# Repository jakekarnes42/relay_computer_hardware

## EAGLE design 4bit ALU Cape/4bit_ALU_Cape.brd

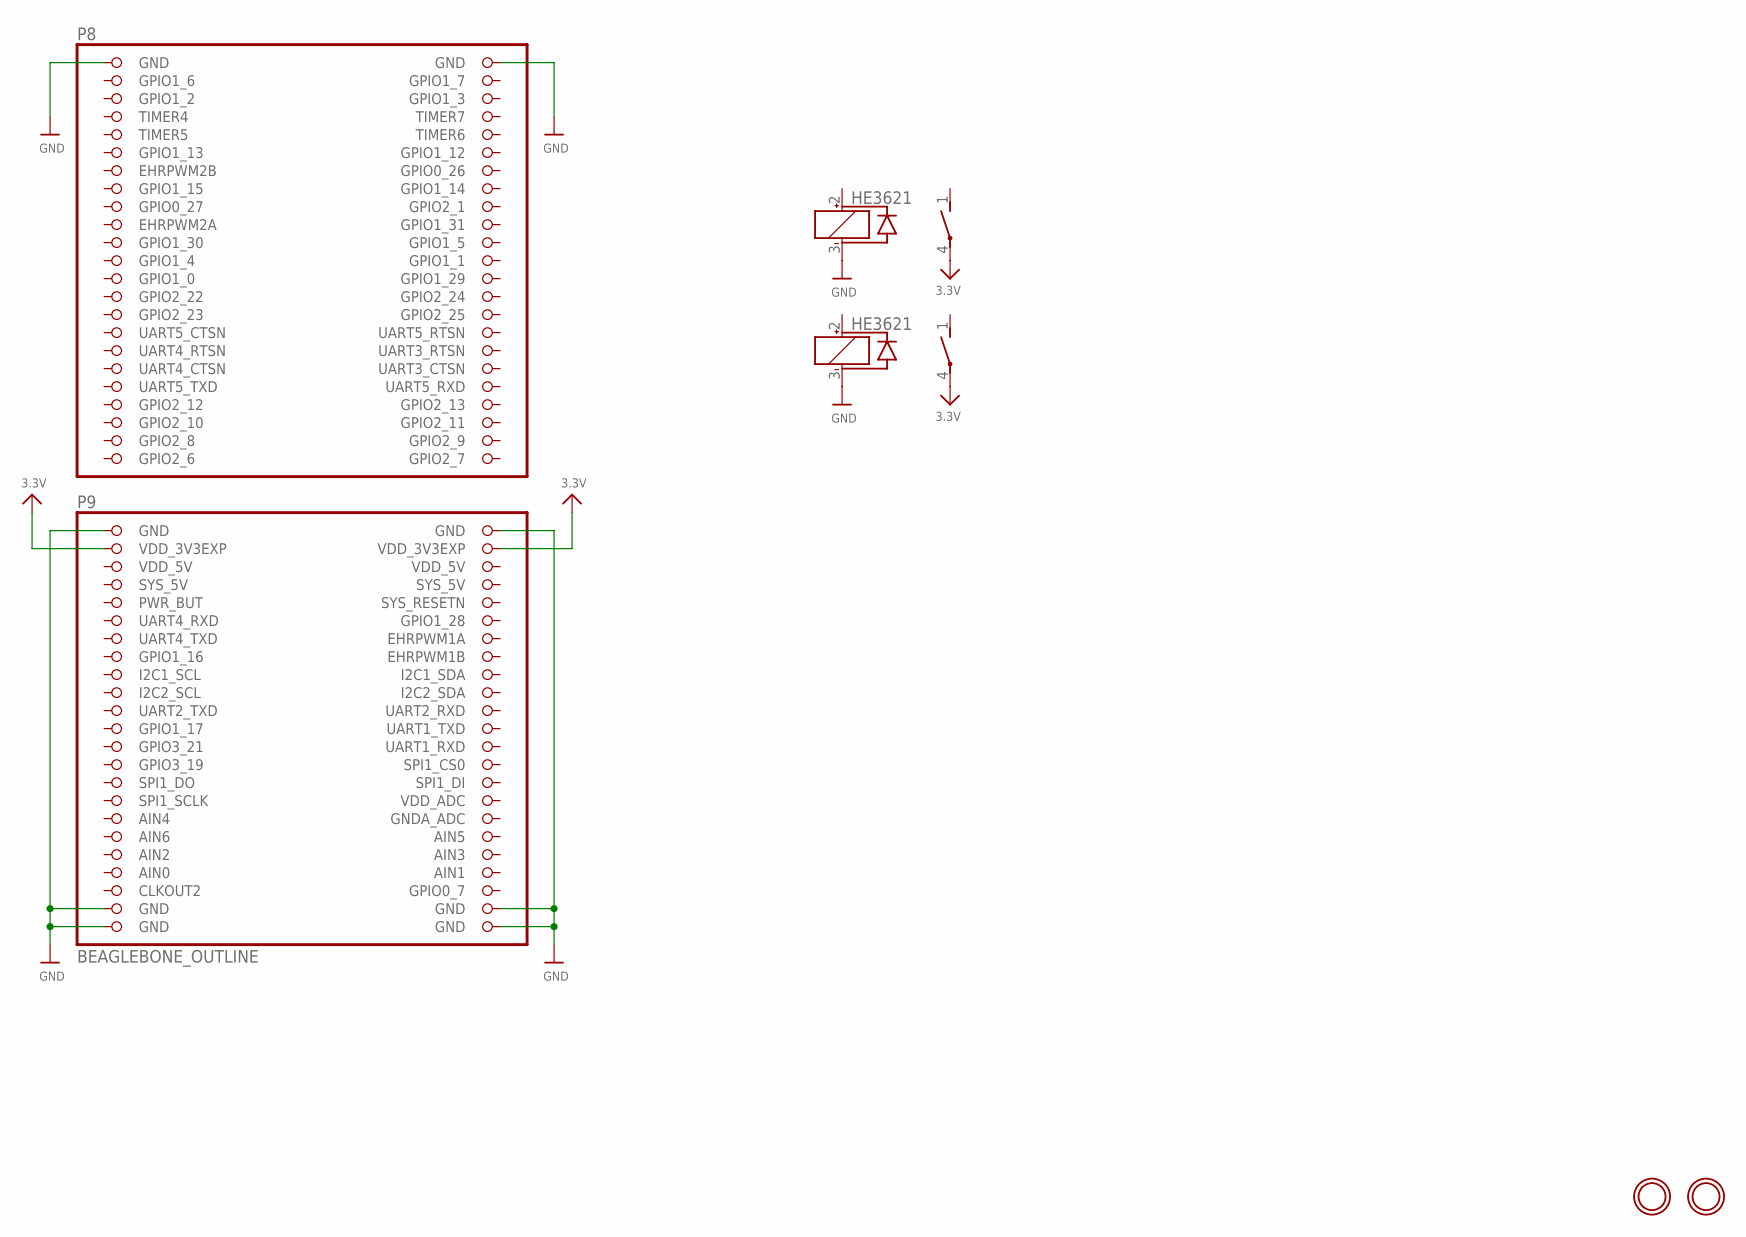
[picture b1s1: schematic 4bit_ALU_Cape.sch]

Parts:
K1, K2: HE3621
U: BEAGLEBONE_OUTLINE; BEAGLEBONE_SHIELD
U$22, U$23: MOUNTINGHOLE3.0THIN; MOUNTINGHOLE_3.0_PLATEDTHIN

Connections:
3.3V: K1.4, K2.4, U.49 (VDD_3V3EXP), U.50 (VDD_3V3EXP)
AIN0: U.85 (AIN0)
AIN3: U.84 (AIN3)
GND: K1.3 (-), K2.3 (-), U.1 (GND), U.2 (GND), U.47 (GND), U.48 (GND), U.89 (GND), U.90 (GND), U.91 (GND), U.92 (GND)
GPIO1_6: U.3 (GPIO1_6)
GPIO1_7: U.4 (GPIO1_7)
GPIO2_6: U.45 (GPIO2_6)
GPIO2_7: U.46 (GPIO2_7)
GPIO2_8: U.43 (GPIO2_8)
GPIO2_9: U.44 (GPIO2_9)
GPIO2_11: U.42 (GPIO2_11)
VDD_5V: U.51 (VDD_5V), U.52 (VDD_5V)

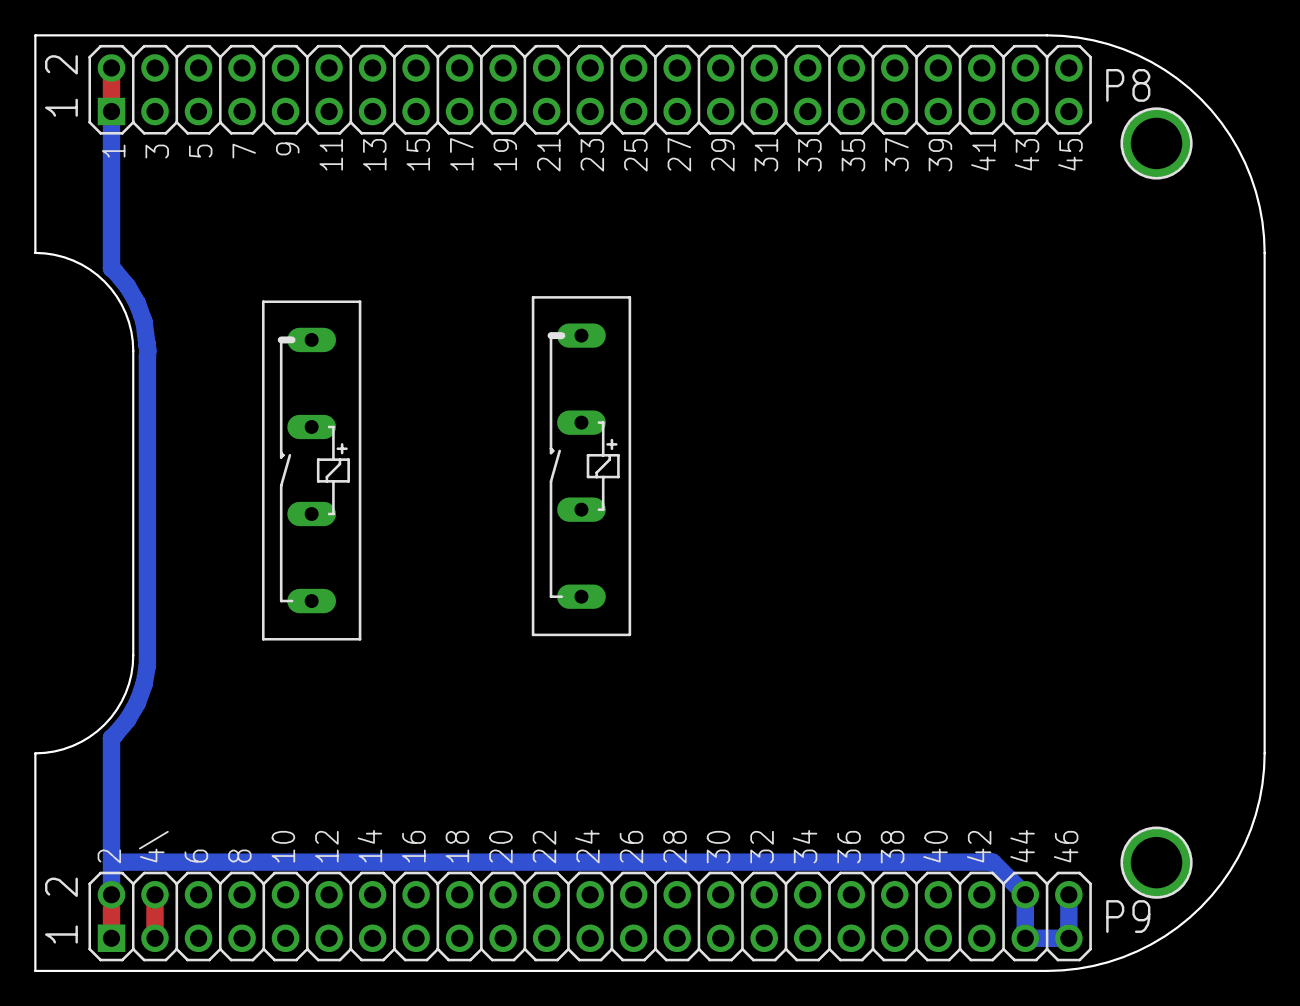
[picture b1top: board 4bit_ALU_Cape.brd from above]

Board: 2 copper layers, 71.8 x 54.6 mm, 5 parts (0 on the bottom side), 3 nets.

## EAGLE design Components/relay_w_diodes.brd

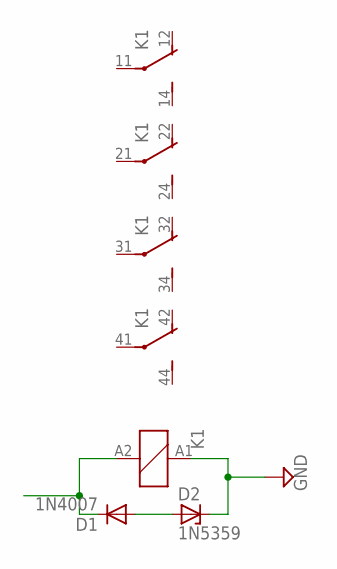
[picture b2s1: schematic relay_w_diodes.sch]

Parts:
D1: 1N4007; DO41-10
D2: 1N5359; C1702-15
K1: PY14-02

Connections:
D$1: D1.A, D2.A
GND: D2.C, K1.A1 (1)
IN: D1.C, K1.A2 (2)

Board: 2 copper layers, 3 parts (0 on the bottom side), 3 nets, no tracks yet.

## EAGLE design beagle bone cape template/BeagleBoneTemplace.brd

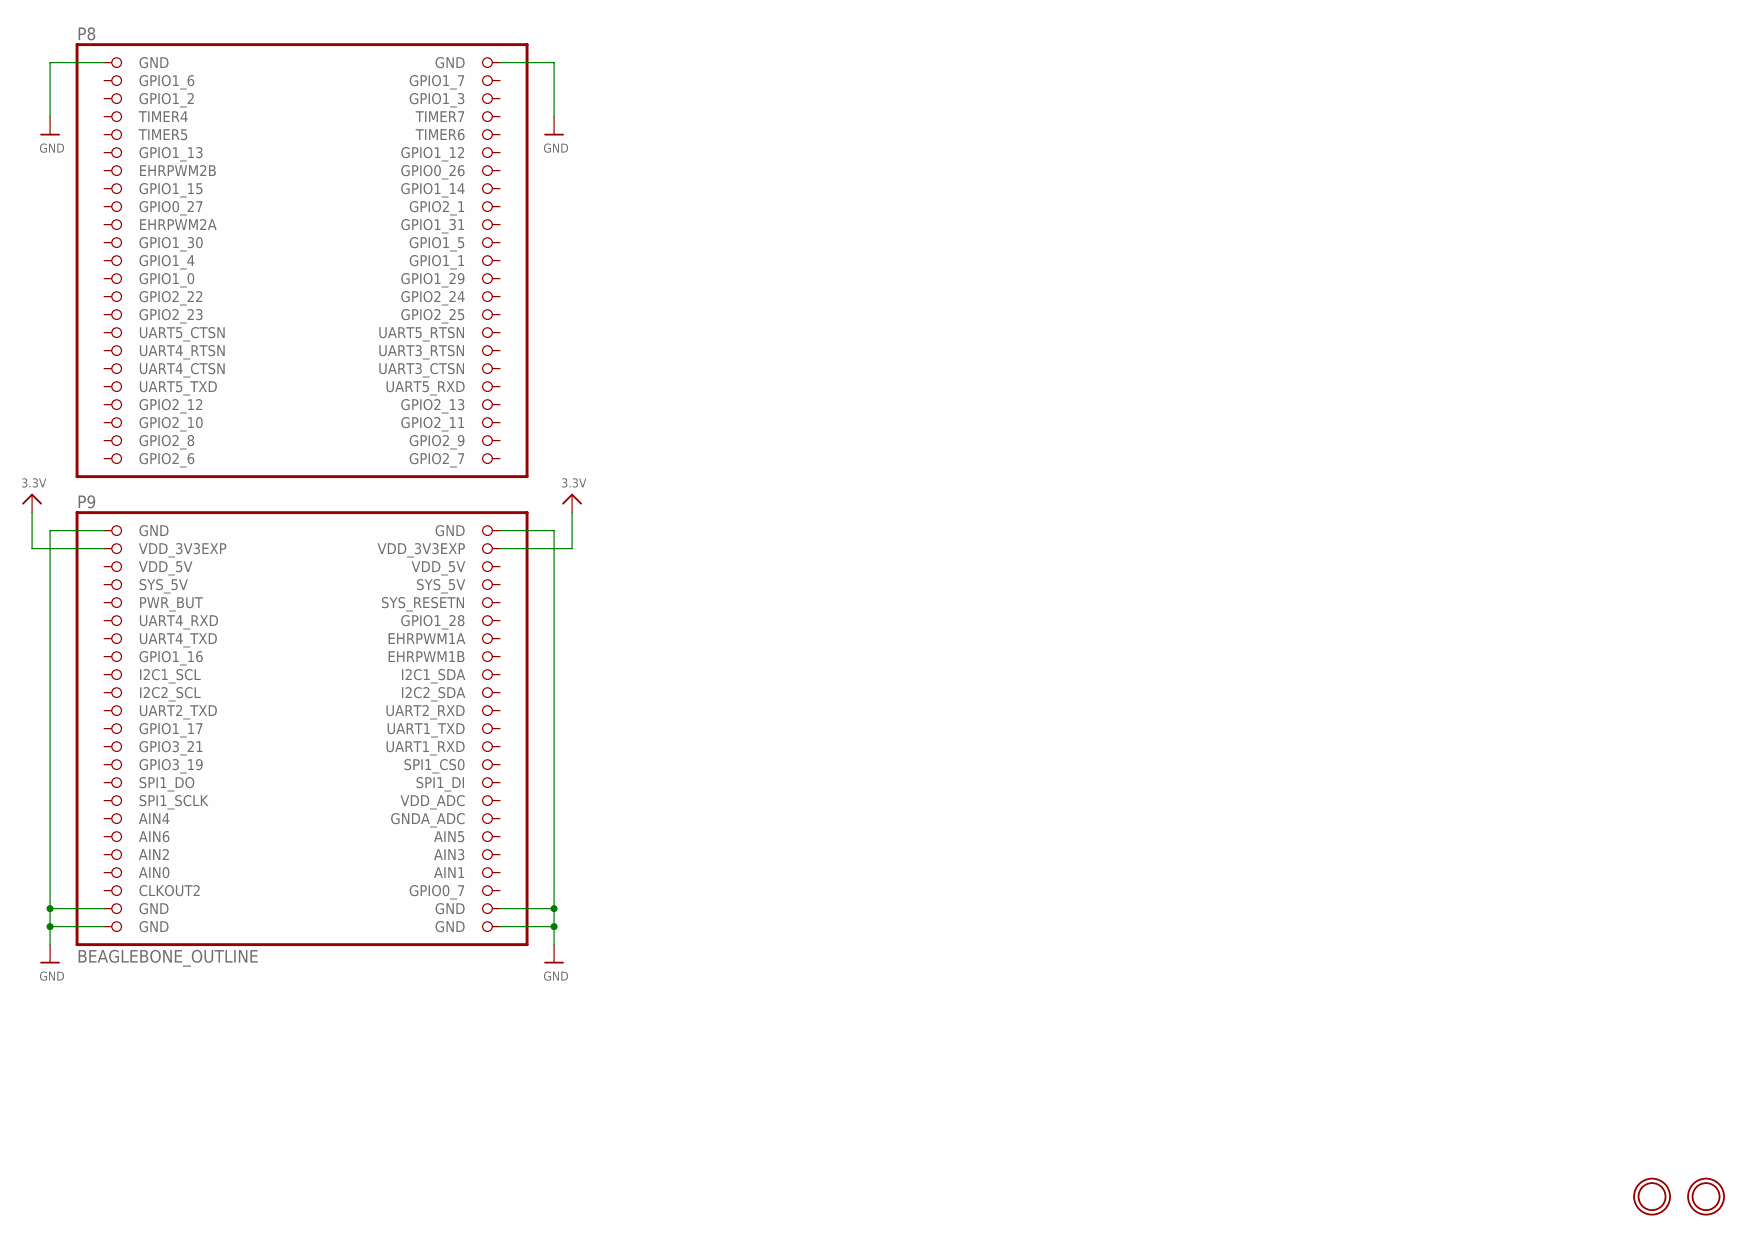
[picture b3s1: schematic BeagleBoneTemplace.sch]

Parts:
U: BEAGLEBONE_OUTLINE; BEAGLEBONE_SHIELD
U$22, U$23: MOUNTINGHOLE3.0THIN; MOUNTINGHOLE_3.0_PLATEDTHIN

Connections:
3.3V: U.49 (VDD_3V3EXP), U.50 (VDD_3V3EXP)
AIN0: U.85 (AIN0)
AIN3: U.84 (AIN3)
GND: U.1 (GND), U.2 (GND), U.47 (GND), U.48 (GND), U.89 (GND), U.90 (GND), U.91 (GND), U.92 (GND)
GPIO1_6: U.3 (GPIO1_6)
GPIO1_7: U.4 (GPIO1_7)
GPIO2_6: U.45 (GPIO2_6)
GPIO2_7: U.46 (GPIO2_7)
GPIO2_8: U.43 (GPIO2_8)
GPIO2_9: U.44 (GPIO2_9)
GPIO2_11: U.42 (GPIO2_11)
VDD_5V: U.51 (VDD_5V), U.52 (VDD_5V)

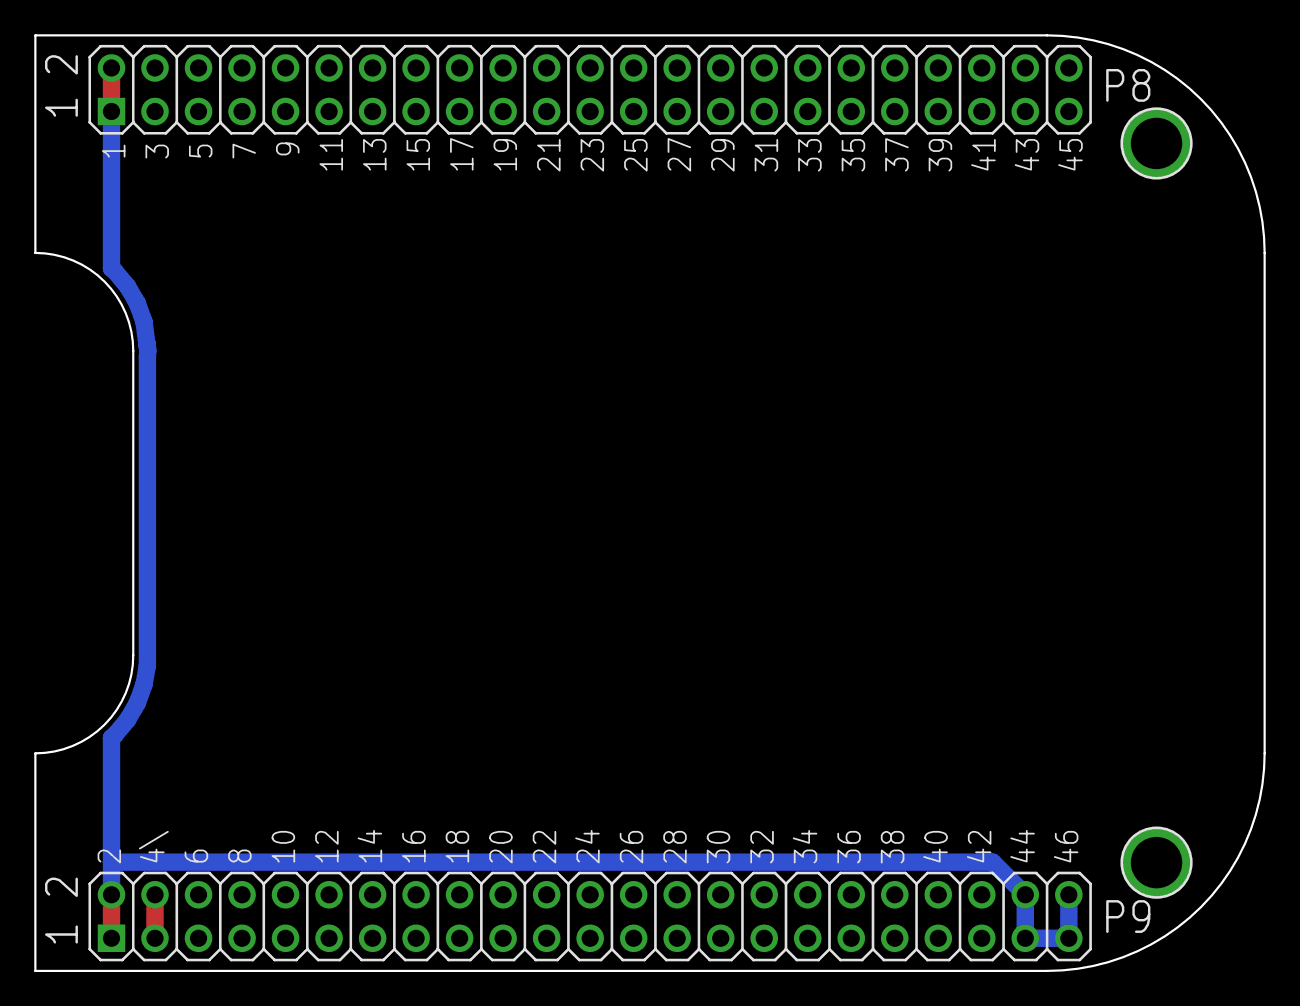
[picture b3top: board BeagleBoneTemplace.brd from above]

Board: 2 copper layers, 71.8 x 54.6 mm, 3 parts (0 on the bottom side), 3 nets.

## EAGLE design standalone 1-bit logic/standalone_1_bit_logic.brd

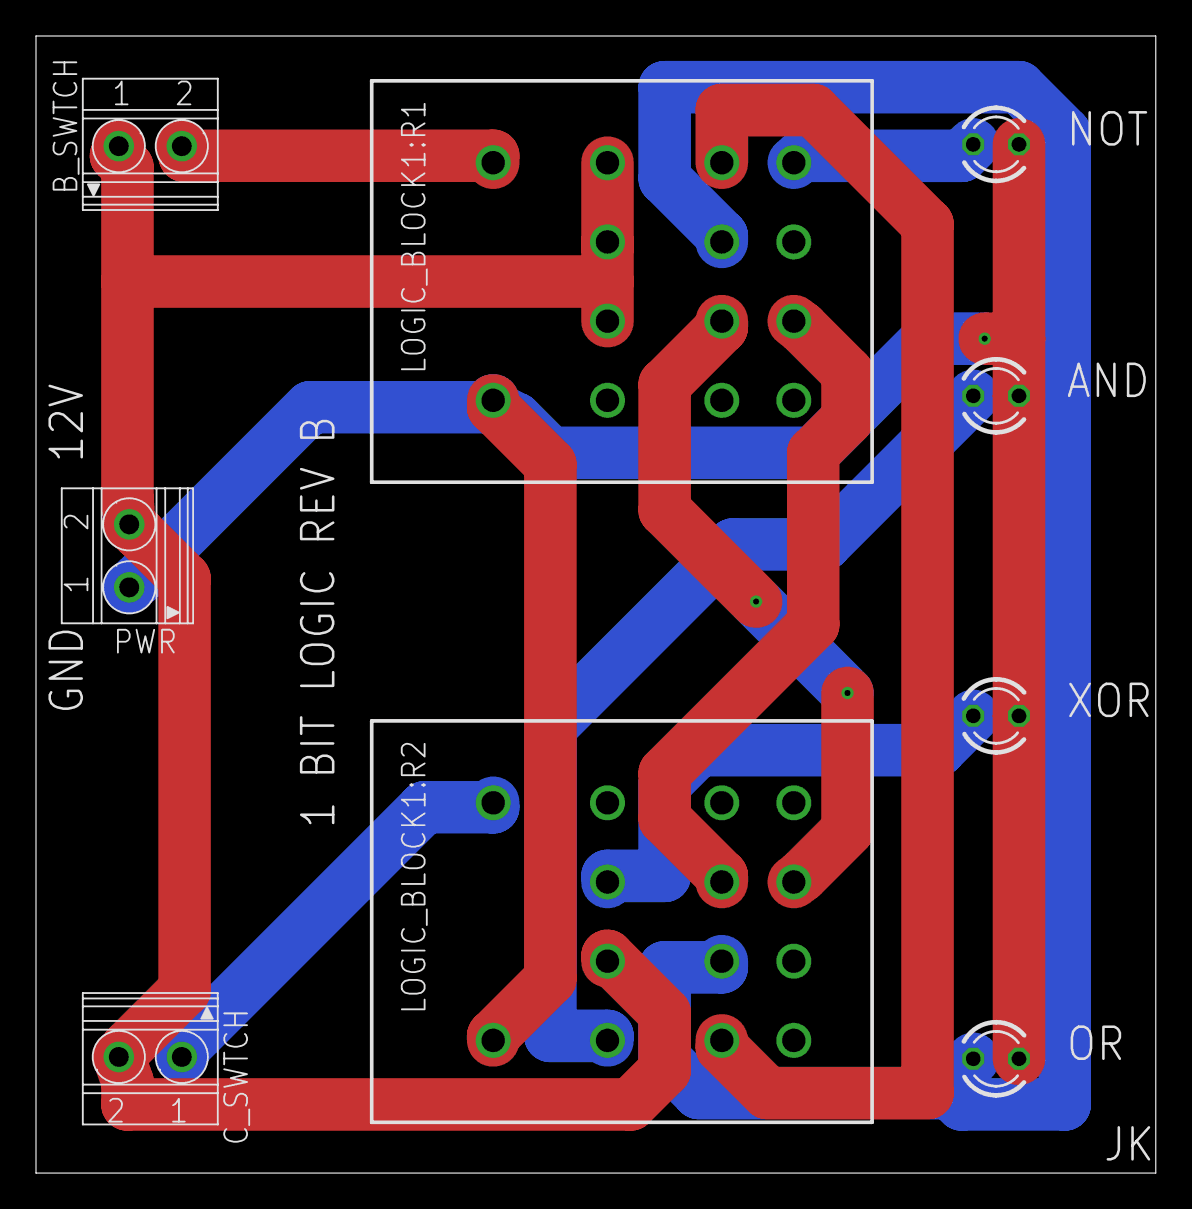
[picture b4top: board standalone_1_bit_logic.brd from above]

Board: 2 copper layers, 62.2 x 63.2 mm, 9 parts (0 on the bottom side), 11 nets.

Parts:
AND_LED: LED3MM
B_SWTCH: SWTCH_BLCK; 1751248
C_SWTCH: SWTCH_BLCK; 1751248
LOGIC_BLOCK1:R1, LOGIC_BLOCK1:R2: PT571R06; PT-4
NOT_LED: LED3MM
OR_LED: LED3MM
PWR: 1751248
XOR_LED: LED3MM

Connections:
+12V: B_SWTCH.1, C_SWTCH.2, LOGIC_BLOCK1:R1.21, LOGIC_BLOCK1:R1.31, LOGIC_BLOCK1:R1.41, LOGIC_BLOCK1:R2.21, PWR.2
AND: AND_LED.A, LOGIC_BLOCK1:R2.11
B: B_SWTCH.2, LOGIC_BLOCK1:R1.A2
C: C_SWTCH.1, LOGIC_BLOCK1:R2.A2
GNDA: AND_LED.K, LOGIC_BLOCK1:R1.A1, LOGIC_BLOCK1:R2.A1, NOT_LED.K, OR_LED.K, PWR.1, XOR_LED.K
LOGIC_BLOCK1:N$1: LOGIC_BLOCK1:R1.24, LOGIC_BLOCK1:R2.32
LOGIC_BLOCK1:N$2: LOGIC_BLOCK1:R1.44, LOGIC_BLOCK1:R2.14
LOGIC_BLOCK1:N$3: LOGIC_BLOCK1:R1.22, LOGIC_BLOCK1:R2.34
NOT: LOGIC_BLOCK1:R1.42, NOT_LED.A
OR: LOGIC_BLOCK1:R1.34, LOGIC_BLOCK1:R2.24, OR_LED.A
XOR: LOGIC_BLOCK1:R2.31, XOR_LED.A
